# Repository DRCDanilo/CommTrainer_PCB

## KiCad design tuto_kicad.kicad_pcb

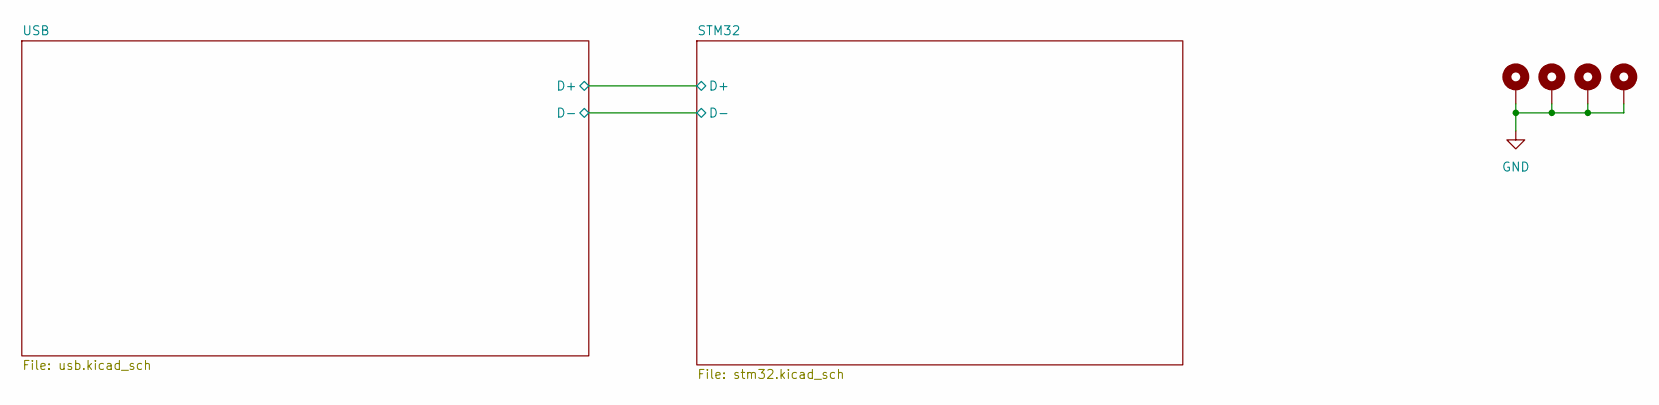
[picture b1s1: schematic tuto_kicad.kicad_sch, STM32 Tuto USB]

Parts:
H101, H102, H103, H104: MountingHole_Pad; MountingHole_3.2mm_M3_Pad_Via

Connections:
GND: H101.1, H102.1, H103.1, H104.1; also elsewhere on the board

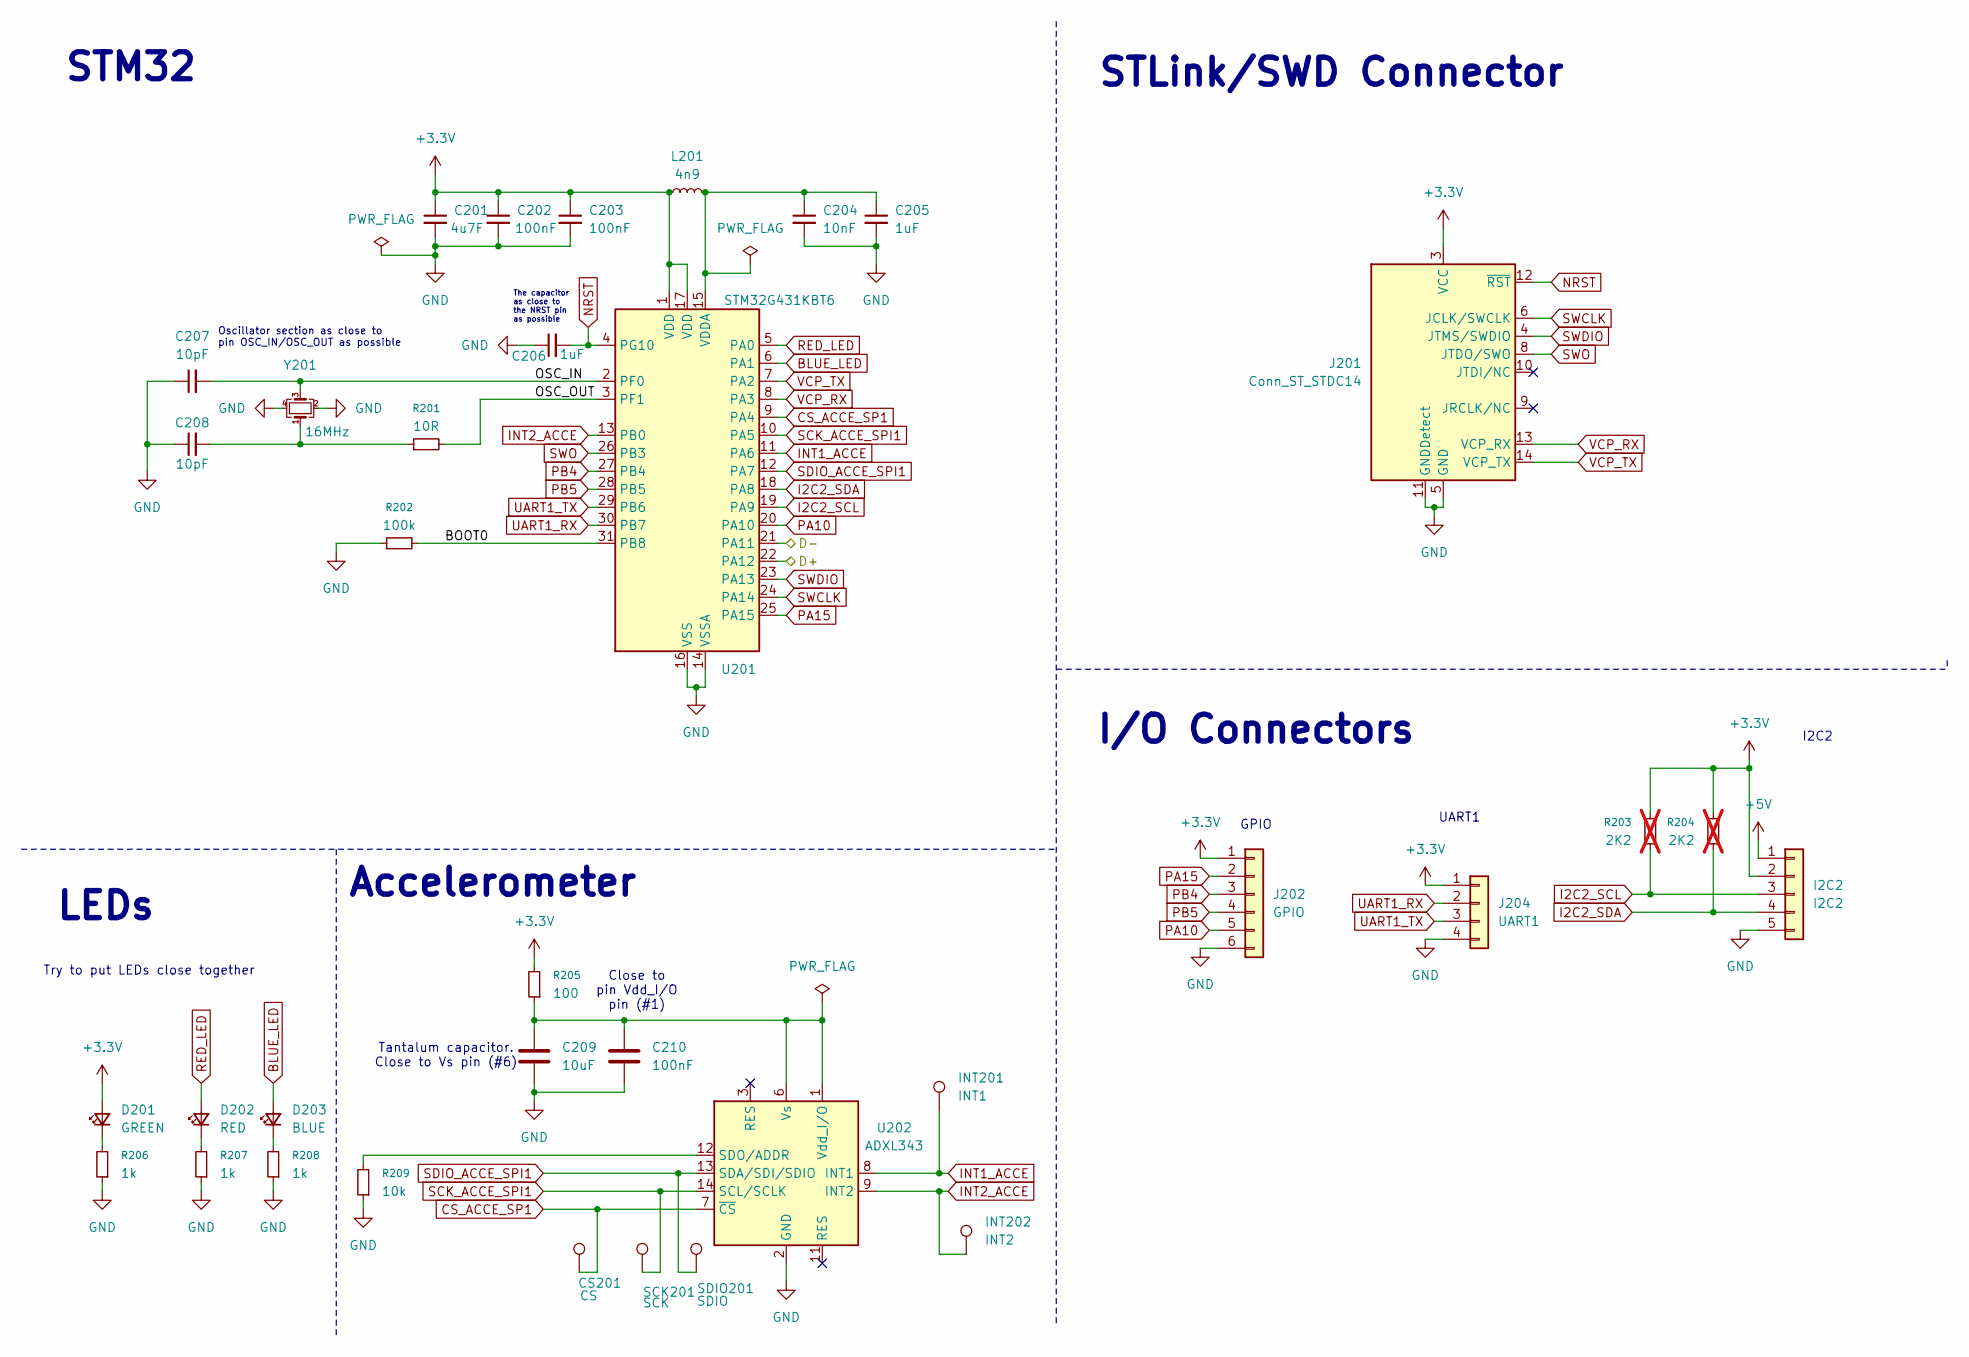
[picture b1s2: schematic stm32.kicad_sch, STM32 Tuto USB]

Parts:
C201: 4u7F; C_0603_1608Metric_Pad1.08x0.95mm_HandSolder
C202, C203: 100nF; C_0603_1608Metric_Pad1.08x0.95mm_HandSolder
C204: 10nF; C_0603_1608Metric_Pad1.08x0.95mm_HandSolder
C205, C206: 1uF; C_0603_1608Metric_Pad1.08x0.95mm_HandSolder
C207, C208: 10pF; C_0603_1608Metric_Pad1.08x0.95mm_HandSolder
C209: 10uF; C_0603_1608Metric
C210: 100nF; C_0603_1608Metric
CS201: CS; TestPoint_Pad_D2.0mm
D201: GREEN; LED_0603_1608Metric_Pad1.05x0.95mm_HandSolder
D202: RED; LED_0603_1608Metric_Pad1.05x0.95mm_HandSolder
D203: BLUE; LED_0603_1608Metric_Pad1.05x0.95mm_HandSolder
I2C2: I2C2; PinHeader_1x05_P2.54mm_Vertical
INT201: INT1; TestPoint_Pad_D2.0mm
INT202: INT2; TestPoint_Pad_D2.0mm
J201: Conn_ST_STDC14; PinHeader_2x07_P1.27mm_Vertical_SMD
J202: GPIO; PinHeader_1x06_P2.54mm_Vertical
J204: UART1; PinHeader_1x04_P2.54mm_Vertical
L201: 4n9; L_0603_1608Metric_Pad1.05x0.95mm_HandSolder
R201: 10R; R_0603_1608Metric_Pad0.98x0.95mm_HandSolder
R202: 100k; R_0603_1608Metric_Pad0.98x0.95mm_HandSolder
R203, R204: 2K2; R_0603_1608Metric; not fitted
R205: 100; R_0603_1608Metric_Pad0.98x0.95mm_HandSolder
R206, R207, R208: 1k; R_0603_1608Metric_Pad0.98x0.95mm_HandSolder
R209: 10k; R_0603_1608Metric_Pad0.98x0.95mm_HandSolder
SCK201: SCK; TestPoint_Pad_D2.0mm
SDIO201: SDIO; TestPoint_Pad_D2.0mm
U201: STM32G431KBT6; LQFP-32_7x7mm_P0.8mm
U202: ADXL343; LGA-14_3x5mm_P0.8mm_LayoutBorder1x6y
Y201: 16MHz; Crystal_SMD_EuroQuartz_MT-4Pin_3.2x2.5mm

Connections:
+3.3V: C201.1, C202.1, C203.1, D201.2 (A), I2C2.2, J201.3 (VCC), J202.1, J204.1, L201.1, R203.1, R204.1, R205.2, U201.1 (VDD), U201.17 (VDD); also elsewhere on the board
+5V: I2C2.1; also elsewhere on the board
/STM32/BOOT0: R202.2, U201.31 (PB8)
/STM32/D+: U201.22 (PA12); also elsewhere on the board
/STM32/D-: U201.21 (PA11); also elsewhere on the board
/STM32/OSC_IN: C207.2, U201.2 (PF0), Y201.3
/STM32/OSC_OUT: R201.2, U201.3 (PF1)
BLUE_LED: D203.2 (A), U201.6 (PA1)
CS_ACCE_SP1: CS201.1, U201.9 (PA4), U202.7 (~CS)
GND: C201.2, C202.2, C203.2, C204.2, C205.2, C206.1, C207.1, C208.1, C209.2, C210.2, I2C2.5, J201.5 (GND), J201.7 (GND), J201.11 (GNDDetect), J202.6, J204.4, R202.1, R206.1, R207.1, R208.1, R209.1, U201.14 (VSSA), U201.16 (VSS), U201.32 (VSS), U202.2 (GND), U202.4 (GND), U202.5 (GND), Y201.2, Y201.4; also elsewhere on the board
I2C2_SCL: I2C2.3, R203.2, U201.19 (PA9)
I2C2_SDA: I2C2.4, R204.2, U201.18 (PA8)
INT1_ACCE: INT201.1, U201.11 (PA6), U202.8 (INT1)
INT2_ACCE: INT202.1, U201.13 (PB0), U202.9 (INT2)
NRST: C206.2, J201.12 (~RST), U201.4 (PG10)
unnamed: C208.2, R201.1, Y201.1
unnamed: D201.1 (K), R206.2
unnamed: D202.1 (K), R207.2
unnamed: D203.1 (K), R208.2
unnamed: C204.1, C205.1, L201.2, U201.15 (VDDA)
unnamed: R209.2, U202.12 (SDO/ADDR)
unnamed: C209.1, C210.1, R205.1, U202.1 (Vdd_I/O), U202.6 (Vs)
PA10: J202.5, U201.20 (PA10)
PA15: J202.2, U201.25 (PA15)
PB4: J202.3, U201.27 (PB4)
PB5: J202.4, U201.28 (PB5)
RED_LED: D202.2 (A), U201.5 (PA0)
SCK_ACCE_SPI1: SCK201.1, U201.10 (PA5), U202.14 (SCL/SCLK)
SDIO_ACCE_SPI1: SDIO201.1, U201.12 (PA7), U202.13 (SDA/SDI/SDIO)
SWCLK: J201.6 (JCLK/SWCLK), U201.24 (PA14)
SWDIO: J201.4 (JTMS/SWDIO), U201.23 (PA13)
SWO: J201.8 (JTDO/SWO), U201.26 (PB3)
UART1_RX: J204.2, U201.30 (PB7); also elsewhere on the board
UART1_TX: J204.3, U201.29 (PB6); also elsewhere on the board
VCP_RX: J201.13 (VCP_RX), U201.8 (PA3)
VCP_TX: J201.14 (VCP_TX), U201.7 (PA2)

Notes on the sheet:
UART1
GPIO
Try to put LEDs close together
Close to pin Vdd_I/O pin (#1)
The capacitor as close to the NRST pin as possible
Tantalum capacitor. Close to Vs pin (#6)
I/O Connectors
STM32
Oscillator section as close to pin OSC_IN/OSC_OUT as possible
I2C2
Accelerometer
STLink/SWD Connector
LEDs

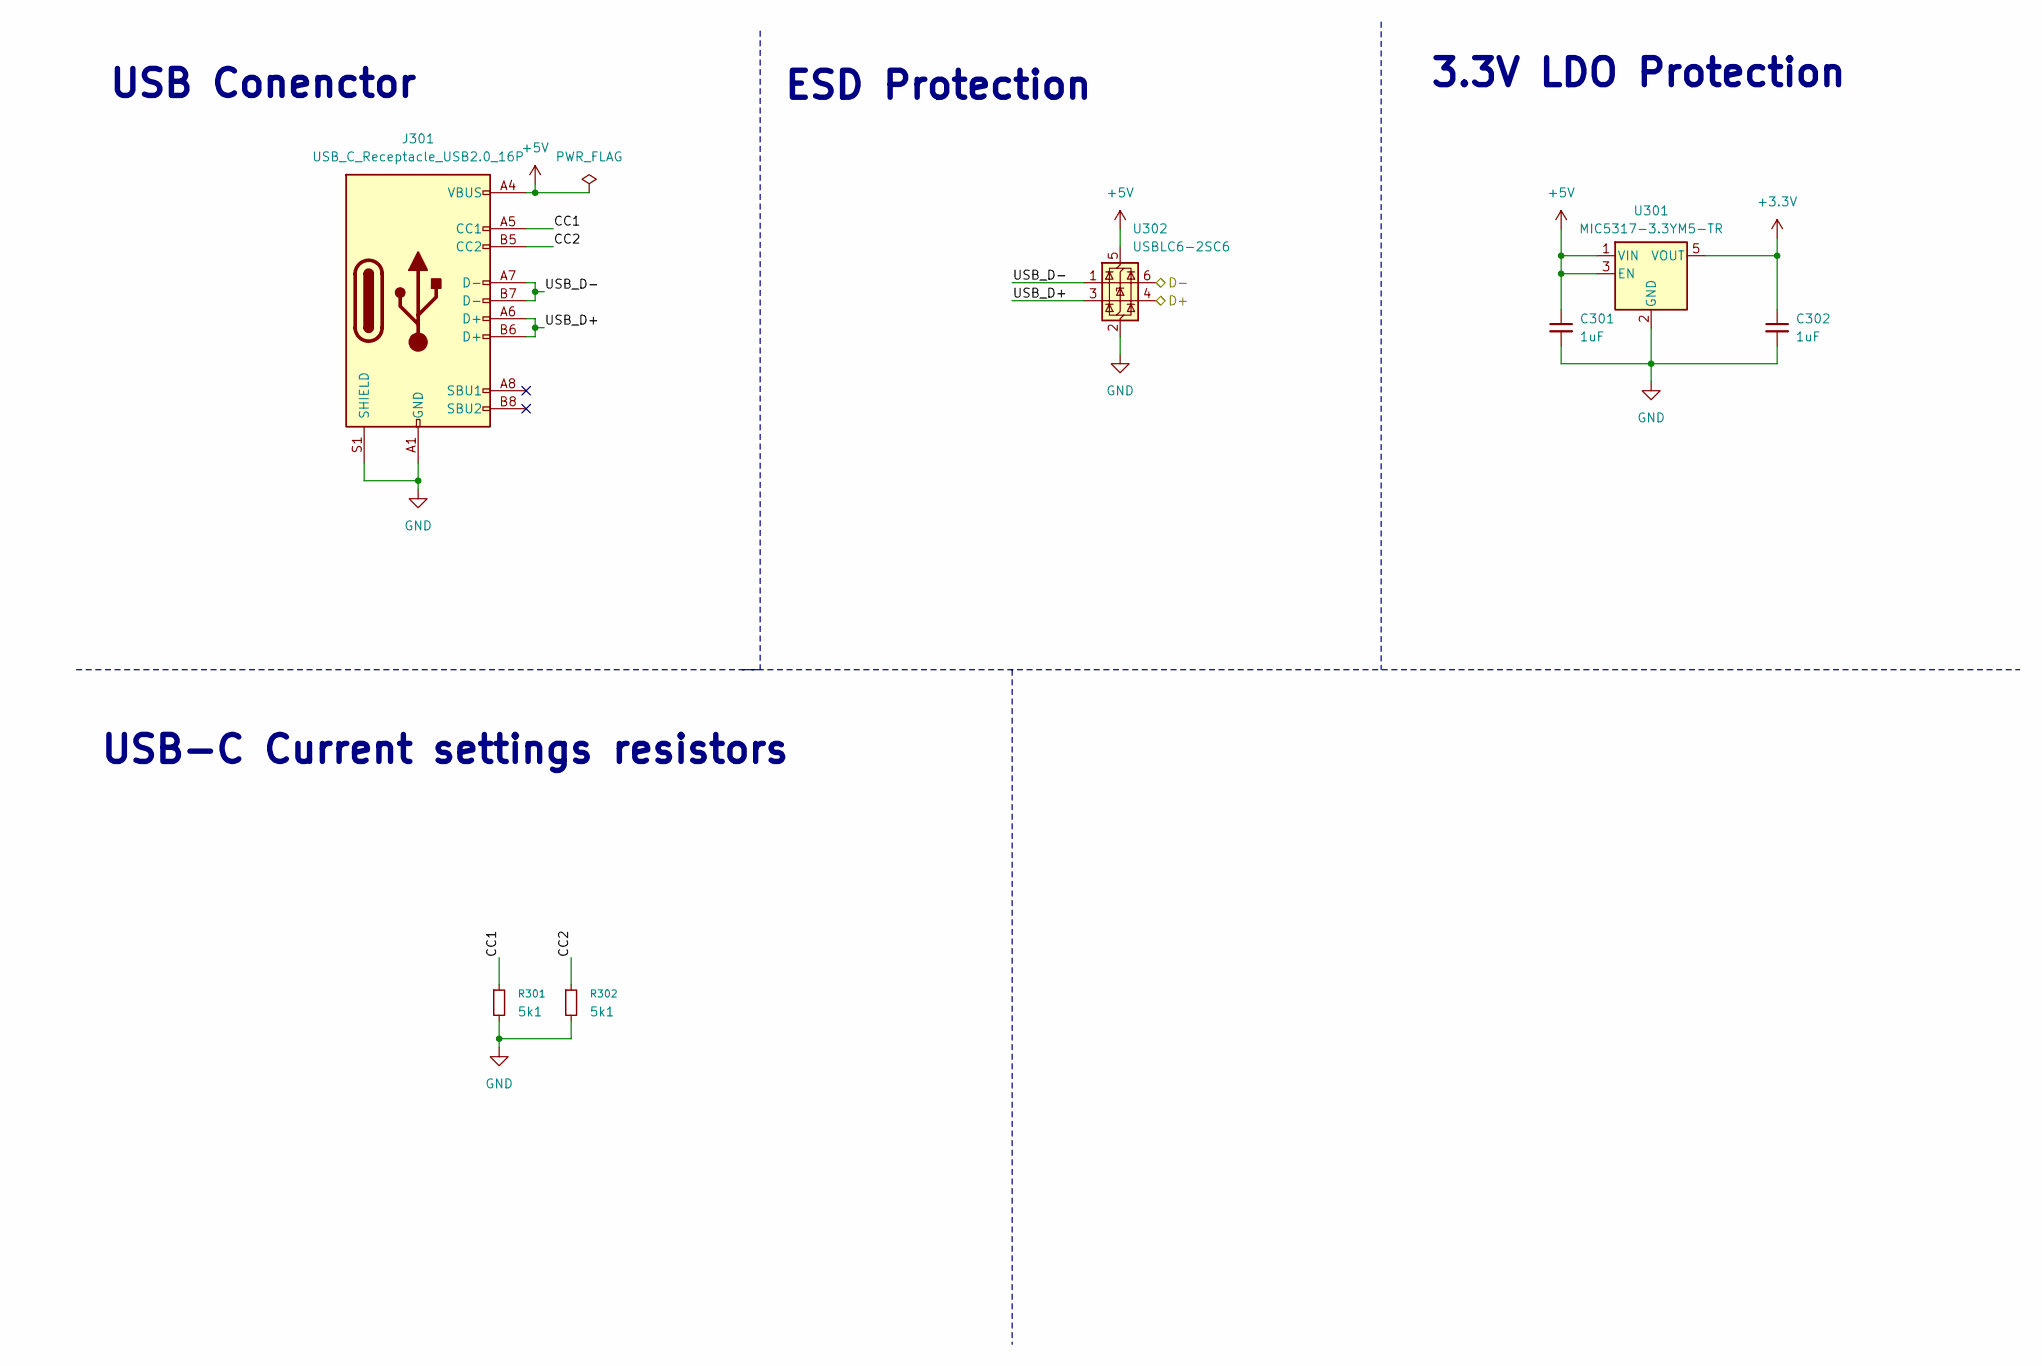
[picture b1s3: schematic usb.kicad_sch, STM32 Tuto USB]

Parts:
C301, C302: 1uF; C_0603_1608Metric_Pad1.08x0.95mm_HandSolder
J301: USB_C_Receptacle_USB2.0_16P; USB_C_Receptacle_GCT_USB4105-xx-A_16P_TopMnt_Horizontal
R301, R302: 5k1; R_0603_1608Metric_Pad0.98x0.95mm_HandSolder
U301: MIC5317-3.3YM5-TR; SOT-23-5
U302: USBLC6-2SC6; SOT-23-6

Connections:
+3.3V: C302.1, U301.5 (VOUT); also elsewhere on the board
+5V: C301.1, J301.A4 (VBUS), J301.A9 (VBUS), J301.B4 (VBUS), J301.B9 (VBUS), U301.1 (VIN), U301.3 (EN), U302.5 (VBUS); also elsewhere on the board
/STM32/D+: U302.4 (I/O2); also elsewhere on the board
/STM32/D-: U302.6 (I/O1); also elsewhere on the board
/USB/CC1: J301.A5 (CC1), R301.1
/USB/CC2: J301.B5 (CC2), R302.1
/USB/USB_D+: J301.A6 (D+), J301.B6 (D+), U302.3 (I/O2)
/USB/USB_D-: J301.A7 (D-), J301.B7 (D-), U302.1 (I/O1)
GND: C301.2, C302.2, J301.A1 (GND), J301.A12 (GND), J301.B1 (GND), J301.B12 (GND), J301.S1 (SHIELD), R301.2, R302.2, U301.2 (GND), U302.2 (GND); also elsewhere on the board

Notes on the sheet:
3.3V LDO Protection
ESD Protection
USB-C Current settings resistors
USB Conenctor

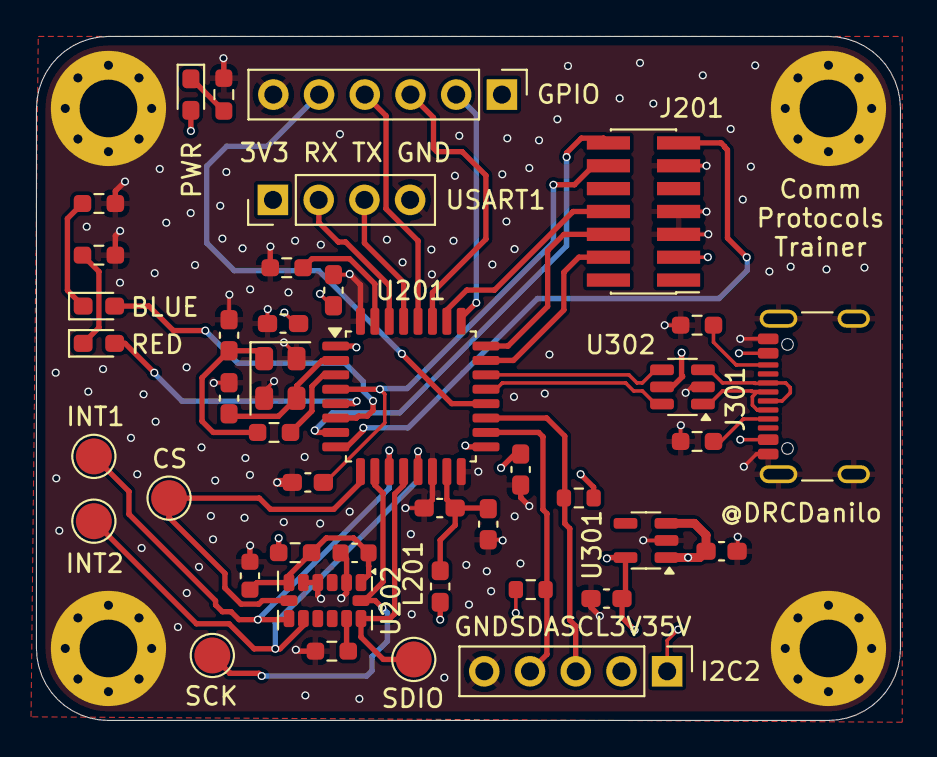
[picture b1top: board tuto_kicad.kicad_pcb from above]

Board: 4 copper layers, 48.0 x 38.0 mm, 46 parts (0 on the bottom side), 40 nets.

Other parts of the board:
USART1: UART1; PinHeader_1x04_P2.54mm_Vertical

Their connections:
+3.3V: USART1.1; also elsewhere on the board
GND: USART1.4; also elsewhere on the board
UART1_RX: USART1.2; also elsewhere on the board
UART1_TX: USART1.3; also elsewhere on the board

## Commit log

2025-10-16 PCB v0.1
2025-10-25 First rev by M. FIACK
2025-10-26 .gitignore file created
2025-10-26 .gitignore file updated
2025-10-26 Pull-up resistors I2C added
2025-10-26 TestPoint in STLink connector deleted
2025-10-26 SPI test points added
2025-10-26 Stop tracking .gitignore files
2025-10-26 backups folder deleted
2025-11-09 SPI test points placed
2025-11-18 USB port placed at PCB edge
2025-11-18 +5V pin added in I2C2 connector
2025-11-19 Silkscreen layers finished
2025-11-19 I2C2 SCL pull-up resistor moved
